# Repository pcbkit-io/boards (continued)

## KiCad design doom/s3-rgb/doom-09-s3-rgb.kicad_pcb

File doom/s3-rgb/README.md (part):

# 09 · s3-rgb — a 4.3" RGB-panel Doom on the ESP32-S3's LCD_CAM

The big-screen variant: the ESP32-S3 scans a **raw RGB TFT** (no controller, no frame memory) out of
a frame buffer in its octal PSRAM with the LCD_CAM peripheral and DMA — the architecture of the
popular ESP32-S3 "4.3-inch" boards. Ten buttons on an I2C expander (the pins all go to the panel),
stereo sound through a DAC and an amplifier, and two 18650 cells it charges from its USB-C port.
JLCPCB assembles everything (matte black mask, ENIG, plated edges); the panel is plugged in and
taped on by hand.

| | |
|---|---|
| Processor | ESP32-S3-WROOM-1-N16R8 (2 × Xtensa LX7 240 MHz, 512 KB SRAM, 16 MB flash, 8 MB octal PSRAM) |
| Display | Newhaven **NHD-4.3-480272EF-ASXP** (IPS; the ASXN it replaces is discontinued): 4.3" 480 × 272, 24-bit RGB parallel, SYNC-DE mode at 8.9 MHz (HSYNC 4 + 39 + 480 + 8, VSYNC 4 + 8 + 272 + 8: 57 Hz, the sheet's typical timing; its line must last 55–65 µs); driven as RGB565 (R3–R7 IO1/2/4/5/6, G2–G7 IO7/15/16/17/18/8, B3–B7 IO9–IO13; PCLK IO42, DE IO40, VSYNC IO41, HSYNC IO39; the low bits grounded) through a 40-pin 0.5 mm FFC connector (Hirose FH34SRJ-40S-0.5SH, top and bottom contacts, 1 mm high) on the front under the panel: the panel's cable folds back under it into the connector, Newhaven's own arrangement |
| Backlight | 12 white LEDs, 25.6 V at 40 mA: **MT3608 boost as a constant-current driver** from SYS (FB regulates 0.6 V over 15 Ω), EN/PWM on IO46 (a strap that must be low at reset: 100 kΩ pull-down); two 2 % zeners in series (18 V + 10 V, 27.3–28.6 V) into FB through 1 kΩ hold the output under the switch's 30 V when no panel is plugged in |
| Input | 10 tact switches on an **MCP23017** (I2C 0x20, IO14 SDA, IO38 SCL), interrupt on change to IO3 |
| Sound | I2S (IO47 BCK, IO48 LRCK, IO21 DIN) → **PCM5102A** DAC → **PAM8403** stereo class-D from SYS (SHDN on 3.3 V: asleep when switched off) (100 kΩ before each input: at most 0.8 W) → two 15 × 15 mm SMD speakers (FS-1540, 8 Ω, C482341) on the back at the two ends, assembled by JLCPCB |
| Power | **2 × 18650 Li-ion in parallel** (1S2P, a 2 A resettable fuse per cell) behind a reverse-cell P-FET (AO3401A) and DW01A + FS8205A protection; USB-C (1 A PTC fuse, TVS, ESD array) → **BQ24075** charger with power path → SYS for the backlight driver and the amplifier → **TLV75733** low-dropout regulator (1 A) for 3.3 V; on/off slide switch on the regulator's EN |
| Programming | USB-C D+/D− to the S3's native USB (IO19/IO20): esptool over USB-Serial/JTAG; RESET (EN) and BOOT (IO0) buttons on the back |
| Board | 182 × 80 mm, **4 layers**, matte black mask, white silkscreen, ENIG, plated edges, four M3 holes; front: the panel on 3 mm foam tape (outline in the silkscreen) over its FFC connector, buttons, the power corner (USB-C at the top edge, charger, CHG/USB LEDs, on/off switch); back: two 18650 holders along the bottom edge, module (antenna past the top edge), protection, regulator, backlight driver, expander, audio, the two speakers, test pads; the PCBKit mark (front, under the D-pad), pcbkit.io (front, between the right-hand buttons); no reference designators on the front |

<!-- STATUS -->
**Board status** (measured on the dev host with PCBKit's CLI): `pcbkit check`: complete — 0 errors, 3 warnings (erc-rail-name), 0 unrouted nets. 106 components, 91 nets, 923 track segments (3760 mm), 135 vias.
`analysis.run { lens: "ready" }`: Typical scenario from the parts' datasheets. Nothing to fix, 4 to consider, 16 ok: weigh the warnings (tell the person about the ones that are their choice), then the board is ready to order.
`pcbkit export --format fab` succeeds without `--force`: every assembled line of the BOM has an LCSC code.
<!-- /STATUS -->

What `check` and the ready lens leave to weigh, and why each is acceptable:

| Warning | Why it is acceptable |
|---|---|
| `diff-pair-uncoupled`, `skew`: DP / DN 18 mm uncoupled (126 mm coupled), 0.7 mm apart in length | USB full speed (12 Mbit/s): the connector is at the top left, the module at the top right; the uncoupled stretch is at the two ends, harmless at 4–20 ns edges |
| BAT's copper heats up by 10 °C (1 A on its thinnest track) | 1 A is the charger's worst case into flat cells; in play the cells give about 0.6 A |
| 6 heat sources need exact thermal parameters | the regulator, charger, boost, amplifier, DAC and module dissipate well under 0.5 W each in this design; the estimate uses generic package limits, as for every board here |

## Run it in the browser

Open https://app.pcbkit.io/github/pcbkit-io/boards/tree/main/doom/s3-rgb, open the
Laboratory and press **Build & run**: the page builds `doom/` for the ESP32-S3's Xtensa LX7 with
Espressif's LLVM (with `DOOM1.WAD` linked into its flash), boots it the way the chip's boot ROM
boots an image from flash, and shows on the panel the frames LCD_CAM scans out of the PSRAM. The
buttons reach the program through the MCP23017, as on the board. Play with the keyboard (arrows,
F fire, Space use, comma/period strafe, M menu, Enter) or a gamepad (`input.js`).

## Why it runs Doom (and what the screen costs)

Doom is the same port as variant 08 (the program and the WAD in place in flash, the zone heap,
screens and visplanes in the octal PSRAM, here at 40 MHz). The difference is the display: the
LCD_CAM peripheral in RGB mode streams a 480 × 272 RGB565 frame buffer from the PSRAM by GDMA
without end, at an 8.9 MHz pixel clock with the Newhaven sheet's typical timing (HSYNC 4 + 39 + 480 + 8,
VSYNC 4 + 8 + 272 + 8): 57 Hz, 261 KB a frame, about 15 MB/s of the PSRAM's ~40 MB/s at 40 MHz
octal DDR (estimate). Each Doom frame is scaled 1.36 times through the palette into the middle
435 × 272 of that buffer and written back from the data cache (the DMA reads the PSRAM, not the
cache). The panel never stops refreshing, which is why this design matters to the simulator: the
display is a **timed bus master**, not a sequence of SPI commands. The ten buttons are read from
the MCP23017 over I2C0 (400 kHz) once a tic. Measured in PCBKit's simulator: the title by 4 s of
device time, the demo by 9 s; 16 s simulated in 12 s.

## Power

Two 18650 Li-ion cells in Keystone 1042 holders on the back, end to end along the bottom edge, in
parallel (1S2P, 3.0–4.2 V, about 5–7 Ah together). From the cells to the loads:

- **Boards ordered before 2026-10-30** (the five of JLCPCB order W2026102705013253) have no per-cell
  fuses and a 28 V 5 % zener on the backlight: put the cells in one at a time and check each against
  the silkscreen's + before inserting the other.
- **Reverse cells:** an AO3401A P-MOSFET in the plus line, its gate at the cells' minus: cells put
  in backwards leave it off and the board unpowered (it conducts both ways when they are right, so
  charging goes through it too). One cell reversed against the other is what the **per-cell fuses**
  are for: each holder's + reaches the pack through its own 2 A resettable fuse (Littelfuse
  1812L200/16GR: 16 V, 100 A interrupting), so a cell put in backwards, or one much fuller than
  the other, trips both in milliseconds instead of shorting the two cells together (tens of
  amperes); take the cell out and they reset. Still put each cell's + at the end the silkscreen
  marks.
- **Protection:** DW01A + FS8205A in the pack's minus: over-charge 4.3 V, over-discharge 2.4 V,
  over-current about 3 A and short circuit, for the pack. Flat-top unprotected 18650 cells fit
  the holders.
- **USB-C input:** 5.1 kΩ on CC1 and CC2 (a sink: 5 V from any charger or computer), a 1 A
  resettable fuse, a 5 V TVS on VBUS and a USBLC6 on D+/D−.
- **Charger with power path:** a TI BQ24075 in USB500 mode (at most 500 mA from the port), 800 mA
  fast charge (RISET 1.13 kΩ), input limit by RILIM 1.18 kΩ, safety timers off (two cells in
  parallel charge longer than its longest timer; termination is by current), TS tied to 10 kΩ (no
  thermistor). Its output SYS runs the board from USB when one is plugged in and from the cells
  through its battery FET otherwise; with more load than USB gives, the cells make up the rest.
- **SYS** feeds the MT3608 backlight driver and the PAM8403 directly (no 5 V rail: both run from
  2.8–5.5 V), and a **TLV75733** (1 A, so the module's 500 mA radio peaks have room; 425 mV
  dropout at 1 A, under 100 mV at this board's ~200 mA) for 3.3 V. It holds 3.3 V down to about 3.4 V of cell; below that the rail follows the
  cells down to 3.0 V, where the ESP32-S3 (3.0–3.6 V) still runs and the cells have under 5 % left.
  The AMS1117 it replaces needs 1.1 V of headroom: straight from the cells it would never make 3.3 V.
- **On/off:** the slide switch on the left edge drives the regulator's EN (100 kΩ holds it low
  between positions). Off, 3.3 V is gone: the module, panel logic, expander and DAC are unpowered,
  the backlight driver's EN is pulled low and the amplifier's SHDN (on 3.3 V) puts it to sleep; the
  cells still charge.

| State | Current (estimate) |
|---|---|
| ESP32-S3 + PSRAM streaming the panel | ~120 mA at 3.3 V |
| Panel logic | 25 mA at 3.3 V |
| Backlight 25.6 V × 40 mA ≈ 1.0 W | ~320 mA from 3.7 V at 85 % |
| PAM8403, moderate volume | ~100 mA |
| **Typical** | **≈ 2.3 W → ~620 mA at 3.7 V** |

Two 3000 mAh cells → **about 9 h** of play (estimate). The TLV75733 burns (3.7 − 3.3) × 0.15 A ≈
0.06 W from the cells (0.3 W from USB).

## Charging

Plug a USB-C charger or computer into the port at the top left. The red LED (CHG) is on while the
cells charge and goes out when they are full; the green LED (USB) is on while USB power is
present. Switched off, the cells take what the port allows in USB500 mode, just under 500 mA: two empty
3000 mAh cells take about 13 h (overnight). Playing
while plugged in, the board takes about 600 mA, more than USB500 mode draws, so the cells hold or
slowly discharge instead of charging. Insert the cells with + at the end the back's silkscreen marks.

## Modules plugged in by hand

- **DS1: the panel**, Newhaven NHD-4.3-480272EF-ASXP (DigiKey, Mouser; its cable and pinout are the
  discontinued ASXN's), bought separately. Lay it face down above the board's top
  edge, its cable toward the board, and push the cable's end straight into J1 (J1 has contacts on
  both sides: either face of the cable works), then close J1's lever. Turn the panel over onto
  the board along the cable's fold and tape it inside its silkscreen outline with 3 mm double-sided
  foam tape on its frame (keep the tape off the cable): the cable then lies folded under the panel,
  as Newhaven's drawing has it. J1 (1 mm high) sits under the panel, and so does one of BT2's
  locating holes (keep the tape clear of it). The panel lies turned half a turn (its cable side,
  the bottom of its scan, at the board's top edge), so the firmware sends the frame out from its
  last pixel to its first.
- **Two 18650 cells.**

## Firmware: build and flash

- **Build:** in PCBKit, the Laboratory's **Build & run** builds `doom/` (Xtensa LX7, Espressif's
  LLVM, the kit's start-up, LCD_CAM/GDMA and I2C drivers); then export the firmware
  (`export.run { format: "firmware" }`): `U1.bin`, the whole flash from offset 0. No 2nd-stage
  bootloader or partition table: the ROM boots the image directly.
- **Flashing on arrival:** switch the board on and plug the USB-C port into a computer: the
  ESP32-S3's built-in USB-Serial/JTAG appears as a serial port (no driver on Linux and macOS; on
  Windows 10+ the class driver); `esptool.py --chip esp32s3 write_flash 0x0 U1.bin` resets it into
  the ROM loader by itself. A fresh module's flash is empty and its ROM loader answers at once. If
  firmware ever takes the USB pins over, hold BOOT (IO0) on the back, press RESET (EN), release
  BOOT: the ROM loader is back. Press RESET: Doom starts.

## Bill of materials

Rough cost at 10 pieces (estimates): ESP32-S3-WROOM-1-N16R8 $4.50 · NHD-4.3-480272EF-ASXP $29 · Hirose
FH34SRJ-40S-0.5SH $0.40 · MT3608 $0.15 · MCP23017 $1.20 ·
PCM5102A $2.00 · PAM8403 $0.15 · BQ24075, protection and TLV75733 $1.60 · USB-C $0.40 · buttons
$3.40 · passives $1.80 · two 18650 holders $9.80 · 4-layer PCB $6.00 · 2 SMD speakers $1.60 → **about
$71** with the Newhaven panel, ~$44 with a generic one, without the cells.

<!-- BOM -->
The assembly BOM as `pcbkit export --format fab` writes it (JLCPCB assembly: LCSC codes; the modules' lines are their sockets):

| Qty | Refs | Part | LCSC | Footprint |
|---|---|---|---|---|
| 2 | BT1, BT2 | 1042 | C5249310 | BatteryHolder_Keystone_1042_1x18650 |
| 1 | C1 | 10uF | C19702 | C_0603_1608Metric |
| 1 | C2 | 22uF | C45783 | C_0805_2012Metric |
| 1 | C3 | 4.7uF | C29823 | C_1206_3216Metric |
| 2 | C4, C22 | 22uF | C12891 | C_1206_3216Metric |
| 7 | C5, C7, C8, C10, C12, C16, C26 | 100nF | C1525 | C_0402_1005Metric |
| 5 | C6, C19, C20, C21, C23 | 1uF | C52923 | C_0402_1005Metric |
| 3 | C9, C11, C13 | 10uF | C15850 | C_0805_2012Metric |
| 2 | C14, C15 | 2.2uF | C87994 | C_0805_2012Metric |
| 2 | C17, C18 | 2.2nF | C1531 | C_0402_1005Metric |
| 2 | C24, C25 | 470nF | C47339 | C_0402_1005Metric |
| 3 | C33, C34, cIn | 1uF | C15849 | C_0603_1608Metric |
| 1 | D1 | 1N5819HW-7-F | C82544 | D_SOD-123 |
| 1 | D2 | zener 18V | C150102 | D_SOD-323 |
| 1 | D3 | zener 10V | C209565 | D_SOD-323 |
| 1 | D6 | tvs 5V | C918844 | D_SOD-323 |
| 1 | F1 | PTC 750mA | C20800 | Fuse_1206_3216Metric |
| 2 | F2, F3 | PTC 2000mA | C18198340 | Fuse_1812_4532Metric |
| 1 | J1 | FH34SRJ-40S-0.5SH(50) | C506798 | Hirose_FH34SRJ-40S-0.5SH_1x40-1MP_P0.50mm_Horizontal |
| 1 | J3 | USB4105-GF-A | C165948 | USB_C_Receptacle_USB2.0_16P |
| 1 | L1 | 22uH | C83472 | L_Power_4x4mm |
| 2 | LS1, LS2 | FS-1540 | C482341 | Speaker_FUET_FS-1540_15x15mm |
| 1 | Q1 | AO3401A | C15127 | SOT-23 |
| 1 | Q2 | FS8205A | C5148694 | TSSOP-8_4.4x2.93mm_P0.65mm |
| 4 | R1, R3, R4, rTs | 10kohm | C25744 | R_0402_1005Metric |
| 5 | R2, R11, R14, R16, R17 | 100kohm | C25741 | R_0402_1005Metric |
| 2 | R5, R6 | 4.7kohm | C25900 | R_0402_1005Metric |
| 2 | R7, R8 | 470ohm | C25117 | R_0402_1005Metric |
| 2 | R9, R10 | 5.1kohm | C25905 | R_0402_1005Metric |
| 1 | R12 | 100ohm | C25076 | R_0402_1005Metric |
| 2 | R13, R15 | 1kohm | C11702 | R_0402_1005Metric |
| 1 | RS1 | 15ohm | C22810 | R_0603_1608Metric |
| 12 | SW1, SW2, SW3, SW4, SW5, SW6, SW7, SW8, SW9, SW10, SW12, SW13 | PTS645SM43SMTR92 LFS | C221880 | SW_Tactile_SPST_6x6mm_SMD |
| 1 | SW11 | MSK12C02 | C431540 | SW_Slide_SPDT_Shouhan_MSK12C02 |
| 1 | U1 | ESP32-S3-WROOM-1-N16R8 | C2913202 | ESP32-S3-WROOM-1_module_18x25.5mm_40_edge_pads_EPAD |
| 1 | U2 | DW01A | C351410 | SOT-6_1.6x2.9mm_P0.95mm |
| 1 | U3 | MCP23017-E/SO | C47023 | SOIC-28W_7.5x17.9mm_P1.27mm |
| 1 | U4 | PCM5102APWR | C107671 | TSSOP-20_4.4x6.5mm_P0.65mm |
| 1 | U5 | PAM8403DR | C17337 | SOIC-16_3.9x9.9mm_P1.27mm |
| 1 | U6 | TLV75733PDBVR | C485517 | SOT-23-5 |
| 1 | U7 | BQ24075RGTR | C15464 | QFN-16-1EP_3x3mm_P0.5mm_EP1.68x1.68mm |
| 1 | U8 | MT3608 | C84817 | SOT-23-6 |
| 1 | U9 | USBLC6-2SC6 | C7519 | SOT-23-6 |
| 2 | cBat, cSys | 4.7uF | C1779 | C_0805_2012Metric |
| 1 | ledChg | red | C2286 | LED_0603_1608Metric |
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
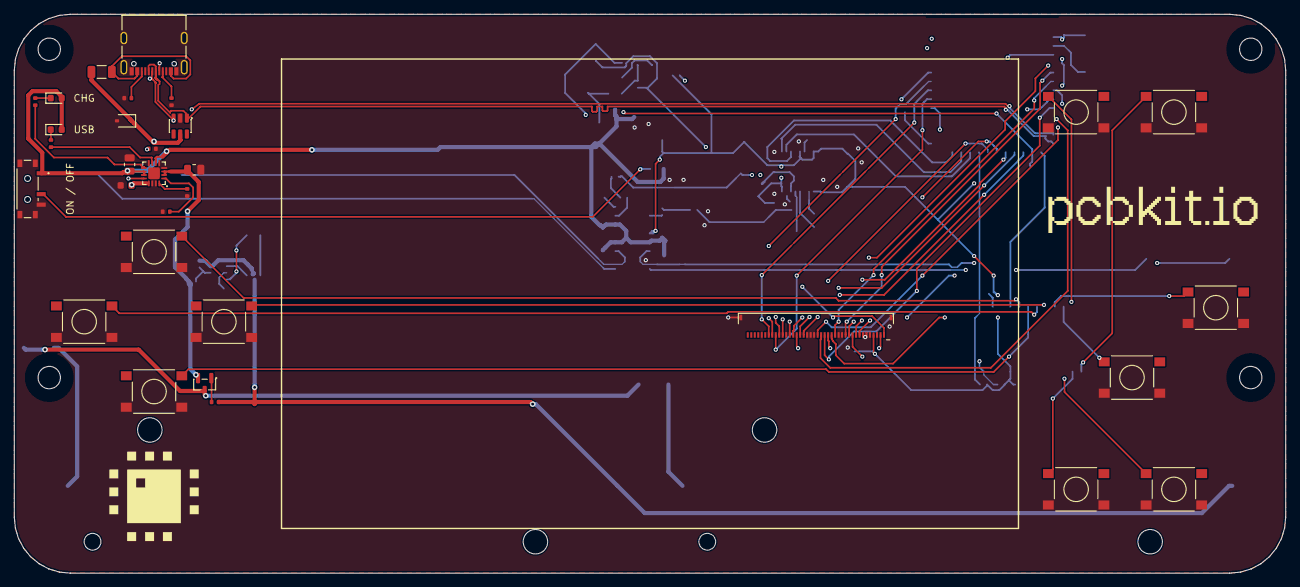
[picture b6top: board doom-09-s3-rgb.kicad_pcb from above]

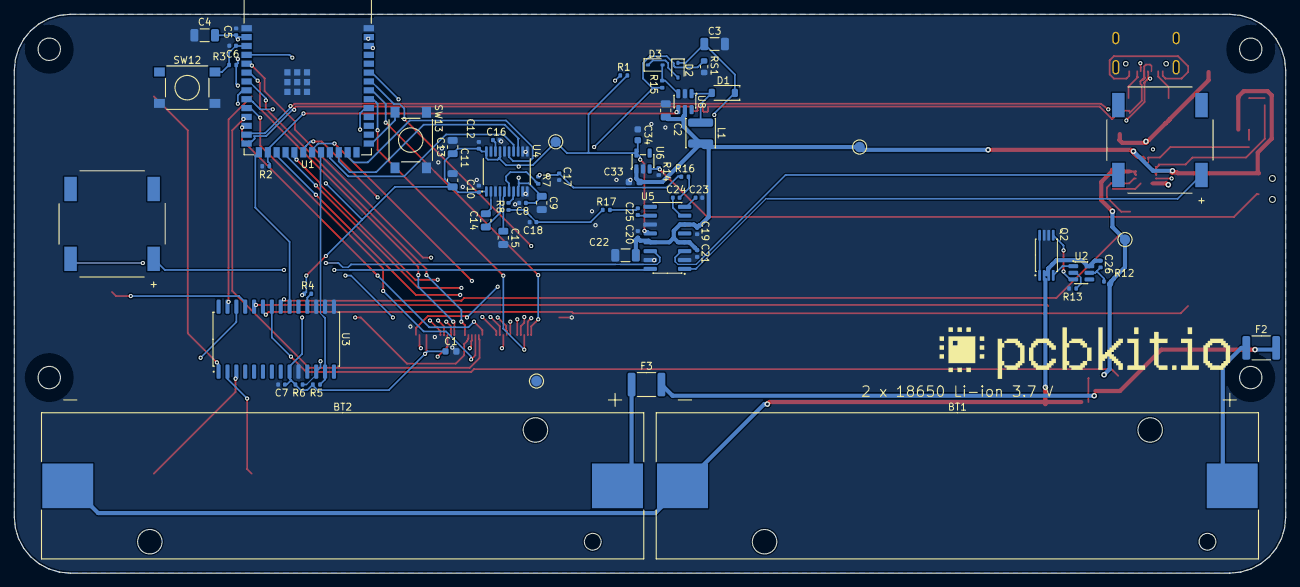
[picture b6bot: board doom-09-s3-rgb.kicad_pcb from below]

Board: 4 copper layers, 182.0 x 80.0 mm, 106 parts (68 on the bottom side), 91 nets.

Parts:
BT1, BT2: 1042; BatteryHolder_Keystone_1042_1x18650
C1: 10uF; C_0603_1608Metric
C2: 22uF; C_0805_2012Metric
C3: 4.7uF; C_1206_3216Metric
C4, C22: 22uF; C_1206_3216Metric
C5, C7, C8, C10, C12, C16, C26: 100nF; C_0402_1005Metric
C6, C19, C20, C21, C23: 1uF; C_0402_1005Metric
C9, C11, C13: 10uF; C_0805_2012Metric
C14, C15: 2.2uF; C_0805_2012Metric
C17, C18: 2.2nF; C_0402_1005Metric
C24, C25: 470nF; C_0402_1005Metric
C33, C34: 1uF; C_0603_1608Metric
D1: 1N5819HW-7-F; D_SOD-123
D2: zener 18V; D_SOD-323
D3: zener 10V; D_SOD-323
D6: tvs 5V; D_SOD-323
DS1: NHD-4.3-480272EF-ASXP; Newhaven_NHD-4.3-480272EF_Panel
F1: PTC 750mA; Fuse_1206_3216Metric
F2, F3: PTC 2000mA; Fuse_1812_4532Metric
H1, H2, H3, H4: MountingHole_3.2mm_M3
J1: FH34SRJ-40S-0.5SH(50); Hirose_FH34SRJ-40S-0.5SH_1x40-1MP_P0.50mm_Horizontal
J3: USB4105-GF-A; USB_C_Receptacle_USB2.0_16P
L1: 22uH; L_Power_4x4mm
LS1, LS2: FS-1540; Speaker_FUET_FS-1540_15x15mm
Q1: AO3401A; SOT-23
Q2: FS8205A; TSSOP-8_4.4x2.93mm_P0.65mm
R1, R3, R4: 10kohm; R_0402_1005Metric
R2, R11, R14, R16, R17: 100kohm; R_0402_1005Metric
R5, R6: 4.7kohm; R_0402_1005Metric
R7, R8: 470ohm; R_0402_1005Metric
R9, R10: 5.1kohm; R_0402_1005Metric
R12: 100ohm; R_0402_1005Metric
R13, R15: 1kohm; R_0402_1005Metric
RS1: 15ohm; R_0603_1608Metric
SW1, SW2, SW3, SW4, SW5, SW6, SW7, SW8, SW9, SW10, SW12, SW13: PTS645SM43SMTR92 LFS; SW_Tactile_SPST_6x6mm_SMD
SW11: MSK12C02; SW_Slide_SPDT_Shouhan_MSK12C02
U1: ESP32-S3-WROOM-1-N16R8; ESP32-S3-WROOM-1_module_18x25.5mm_40_edge_pads_EPAD
U2: DW01A; SOT-6_1.6x2.9mm_P0.95mm
U3: MCP23017-E/SO; SOIC-28W_7.5x17.9mm_P1.27mm
U4: PCM5102APWR; TSSOP-20_4.4x6.5mm_P0.65mm
U5: PAM8403DR; SOIC-16_3.9x9.9mm_P1.27mm
U6: TLV75733PDBVR; SOT-23-5
U7: BQ24075RGTR; QFN-16-1EP_3x3mm_P0.5mm_EP1.68x1.68mm
U8: MT3608; SOT-23-6
U9: USBLC6-2SC6; SOT-23-6
cBat: 4.7uF; C_0805_2012Metric
cIn: 1uF; C_0603_1608Metric
cSys: 4.7uF; C_0805_2012Metric
ledChg: red; LED_0603_1608Metric
ledPg: green; LED_0603_1608Metric
logo: Logo_PCBKit_pcbkit.io
mark: Logo_PCBKit_mark
rChg: 1.5kohm; R_0402_1005Metric
rIlim: 1.18kohm; R_0402_1005Metric
rIset: 1.13kohm; R_0402_1005Metric
rPg: 1.5kohm; R_0402_1005Metric
rTs: 10kohm; R_0402_1005Metric
tpBat: TestPoint_Round_D1.5mm
tpGnd: TestPoint_Round_D1.5mm
tpSys: TestPoint_Round_D1.5mm
tpV3: TestPoint_Round_D1.5mm
wordmark: Logo_PCBKit_wordmark

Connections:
AMP_L: C24.2 (b), R16.2 (b)
AMP_R: C25.2 (b), R17.2 (b)
BAT: Q1.2 (S), R12.1 (a), U7.2 (BAT), U7.3 (BAT), cBat.1 (a), tpBat.1
BAT_IN: F2.2 (b), F3.2 (b), Q1.3 (D)
BLU3: J1.24 (B3), U1.17 (IO9)
BLU4: J1.25 (B4), U1.18 (IO10)
BLU5: J1.26 (B5), U1.19 (IO11)
BLU6: J1.27 (B6), U1.20 (IO12)
BLU7: J1.28 (B7), U1.21 (IO13)
BL_EN: R2.1 (a), U1.16 (IO46), U8.4 (EN)
BL_FB: D3.2 (A), R15.2 (b), U8.3 (FB)
BL_OVP: D2.2 (A), D3.1 (K)
BL_SW: D1.2 (A), L1.2 (b), U8.1 (SW)
CELL1_P: BT1.2 (C2), F2.1 (a)
CELL2_P: BT2.2 (C2), F3.1 (a)
CELL_N: BT1.1 (C1), BT2.1 (C1), C26.1 (a), Q2.2 (S1), Q2.3 (S1), R11.1 (a), U2.6 (GND)
CHG_LED: ledChg.1 (K), rChg.2 (b)
CHG_N: U7.9 (nCHG), rChg.1 (a)
DAC_1V8: C16.1 (a), U4.18 (LDOO)
DAC_VNEG: C15.1 (a), U4.5 (VNEG)
DE: J1.34 (DEN), U1.33 (IO40)
DISP: J1.31 (DISP), R1.2 (b)
DN: J3.A7 (DN), J3.B7 (DN), U1.13 (IO19), U9.3 (IO2)
DOWN: SW2.1 (a), U3.22 (GPA1)
DP: J3.A6 (DP), J3.B6 (DP), U1.14 (IO20), U9.1 (IO1)
EN: C6.1 (a), R3.2 (b), SW12.1 (a), U1.3 (EN)
ENTER: SW10.1 (a), U3.3 (GPB2)
FIRE: SW7.1 (a), U3.25 (GPA4)
GND: C1.2 (b), C2.2 (b), C3.2 (b), C4.2 (b), C5.2 (b), C6.2 (b), C7.2 (b), C8.2 (b), C9.2 (b), C10.2 (b), C11.2 (b), C12.2 (b), C13.2 (b), C15.2 (b), C16.2 (b), C17.2 (b), C18.2 (b), C19.2 (b), C20.2 (b), C21.2 (b), C22.2 (b), C23.2 (b), C33.2 (b), C34.2 (b), D6.2 (A), J1.3 (GND), J1.5 (R0), J1.6 (R1), J1.7 (R2), J1.13 (G0), J1.14 (G1), J1.21 (B0), J1.22 (B1), J1.23 (B2), J1.29 (GND), J1.36 (GND), J1.MP, J3.A1 (GND), J3.A12, J3.B1 (GND), J3.B12, J3.S1 (SHIELD), Q2.6 (S2), Q2.7 (S2), R2.2 (b), R9.2 (b), R10.2 (b), R13.2 (b), R14.2 (b), RS1.2 (b), SW1.2 (b), SW2.2 (b), SW3.2 (b), SW4.2 (b), SW5.2 (b), SW6.2 (b), SW7.2 (b), SW8.2 (b), SW9.2 (b), SW10.2 (b), SW11.3 (B), SW11.4 (SHELL), SW12.2 (b), SW13.2 (b), U1.1 (GND), U1.40 (GND), U1.41 (GND), U3.10 (VSS), U3.15 (A0), U3.16 (A1), U3.17 (A2), U4.3 (CPGND), U4.9 (AGND), U4.10 (DEMP), U4.11 (FLT), U4.12 (SCK), U4.16 (FMT), U4.19 (DGND), U5.2 (PGND), U5.11 (GND), U5.15 (PGND), U6.2 (GND), U7.4 (nCE), U7.5 (EN2), U7.8 (VSS), U7.14 (TMR), U7.15 (SYSOFF), U7.17 (VSS), U8.2 (GND), U9.2 (GND), cBat.2 (b), cIn.2 (b), cSys.2 (b), rIlim.2 (b), rIset.2 (b), rTs.2 (b), tpGnd.1
GRN2: J1.15 (G2), U1.7 (IO7)
GRN3: J1.16 (G3), U1.8 (IO15)
GRN4: J1.17 (G4), U1.9 (IO16)
GRN5: J1.18 (G5), U1.10 (IO17)
GRN6: J1.19 (G6), U1.11 (IO18)
GRN7: J1.20 (G7), U1.12 (IO8)
HSYNC: J1.32 (HSYNC), U1.32 (IO39)
I2S_BCK: U1.24 (IO47), U4.13 (BCK)
I2S_DIN: U1.23 (IO21), U4.14 (DIN)
I2S_LRCK: U1.25 (IO48), U4.15 (LRCK)
ILIM: U7.12 (ILIM), rIlim.1 (a)
ISET: U7.16 (ISET), rIset.1 (a)
KEYS_INT: U1.15 (IO3), U3.20 (INTA)
LDO_EN: R14.1 (a), SW11.2 (COM), U6.3 (EN)
LED_A: C3.1 (a), D1.1 (K), D2.1 (K), J1.2 (LED_A)
LED_K: J1.1 (LED_K), R15.1 (a), RS1.1 (a)
LEFT: SW3.1 (a), U3.23 (GPA2)
LINE_L: C17.1 (a), R7.1 (a), R16.1 (a)
LINE_R: C18.1 (a), R8.1 (a), R17.1 (a)
MENU: SW9.1 (a), U3.2 (GPB1)
unnamed: C14.2 (b), U4.2 (CAPP)
unnamed: C14.1 (a), U4.4 (CAPM)
unnamed: C23.1 (a), U5.8 (VREF)
unnamed: C24.1 (a), U5.7 (INL)
unnamed: C25.1 (a), U5.10 (INR)
unnamed: C26.2 (b), R12.2 (b), U2.5 (VCC)
unnamed: Q2.4 (G1), U2.1 (OD)
unnamed: Q2.5 (G2), U2.3 (OC)
unnamed: R4.2 (b), U3.18 (RESET)
unnamed: R7.2 (b), U4.6 (OUTL)
unnamed: R8.2 (b), U4.7 (OUTR)
unnamed: R13.1 (a), U2.2 (CS)
unnamed: SW13.1 (a), U1.27 (IO0)
PCLK: J1.30 (CLK), U1.35 (IO42)
PG_LED: ledPg.1 (K), rPg.1 (a)
PG_N: U7.7 (nPGOOD), rPg.2 (b)
RED3: J1.8 (R3), U1.39 (IO1)
RED4: J1.9 (R4), U1.38 (IO2)
RED5: J1.10 (R5), U1.4 (IO4)
RED6: J1.11 (R6), U1.5 (IO5)
RED7: J1.12 (R7), U1.6 (IO6)
RIGHT: SW4.1 (a), U3.24 (GPA3)
SCL: R6.1 (a), U1.31 (IO38), U3.12 (SCL)
SDA: R5.1 (a), U1.22 (IO14), U3.13 (SDA)
SPK_LN: LS1.1 (N), U5.3 (OUTLN)
SPK_LP: LS1.2, U5.1 (OUTLP)
SPK_RN: LS2.1 (N), U5.14 (OUTRN)
SPK_RP: LS2.2, U5.16 (OUTRP)
STRAFE_L: SW5.1 (a), U3.27 (GPA6)
STRAFE_R: SW6.1 (a), U3.1 (GPB0)
SYS: C2.1 (a), C19.1 (a), C20.1 (a), C21.1 (a), C22.1 (a), C33.1 (a), L1.1 (a), SW11.1 (A), U5.4 (PVDD), U5.6 (VDD), U5.13 (PVDD), U6.1 (IN), U7.6 (EN1), U7.10 (OUT), U7.11 (OUT), U8.5 (VIN), cSys.1 (a), ledChg.2 (A), ledPg.2 (A), tpSys.1
TS: U7.1 (TS), rTs.1 (a)
U2Support/DRAIN: Q2.1 (D12), Q2.8 (D12)
UP: SW1.1 (a), U3.21 (GPA0)
USE: SW8.1 (a), U3.26 (GPA5)
V3: C1.1 (a), C4.1 (a), C5.1 (a), C7.1 (a), C8.1 (a), C9.1 (a), C10.1 (a), C11.1 (a), C12.1 (a), C13.1 (a), C34.1 (a), J1.4 (VDD), R1.1 (a), R3.1 (a), R4.1 (a), R5.2 (b), R6.2 (b), U1.2 (P3V3), U3.9 (VDD), U4.1 (CPVDD), U4.8 (AVDD), U4.17 (XSMT), U4.20 (DVDD), U5.12 (SHDN), U6.5 (OUT), tpV3.1
VBUS: D6.1 (K), F1.2 (b), U7.13 (IN), U9.5 (VBUS), cIn.1 (a)
VSYNC: J1.33 (VSYNC), U1.34 (IO41)
reversed/gate: Q1.1 (G), R11.2 (b)
usb/power/cc1: J3.A5 (CC1), R9.1 (a)
usb/power/cc2: J3.B5 (CC2), R10.1 (a)
usb/power/vbusIn: F1.1 (a), J3.A4 (VBUS), J3.A9, J3.B4 (VBUS), J3.B9

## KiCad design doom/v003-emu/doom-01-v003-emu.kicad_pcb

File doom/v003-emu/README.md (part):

# 01 · v003-emu — Doom on a 10-cent RISC-V, by emulation

The most primitive variant: a WCH CH32V003 cannot hold Doom (2 KB of RAM), so it does not try.
Its firmware is a small RV32IMA interpreter; the real program — Doom built for a plain RV32 machine
— lives in an 8 MB SPI PSRAM and boots from a 16 MB SPI flash. It is the "Linux on an 8-bit AVR"
trick applied to Doom: slow (well under one frame per second, estimate below), but every part is a
real, orderable chip, and it is the clearest test of whether PCBKit's engine models *buses* rather
than *programs*.

| | |
|---|---|
| Processor | WCH CH32V003F4P6, QingKe V2A core: RISC-V **RV32EC** (16 registers, compressed) + WCH's XW byte/halfword extension, 48 MHz (24 MHz HSI × 2 PLL), 2 KB SRAM, 16 KB flash, TSSOP-20 |
| Memory | APS6404L-3SQR 8 MB PSRAM (guest RAM) and W25Q128JV 16 MB NOR flash (guest kernel + WAD), both on SPI1 (PC5/PC6/PC7) with their own chip selects (PC0, PC4) |
| Display | Nokia 5110 module, PCD8544, 84 × 48 monochrome, SPI shared with the memories (CS PC3, D/C PC2), reset by RC at power-up |
| Input | 8 tact switches (5.1 mm) to GND, internal pull-ups: PD0, PD2–PD6, PA1, PA2 (the crystal pins are free: the HSI runs the chip) |
| Sound | passive piezo on PC1 (TIM2 CH4 remap) |
| Power | 2 × 18650 Li-ion in parallel (1S2P, a 2 A resettable fuse per cell) behind reverse-cell (AO3401A) and DW01A + FS8205A protection; BQ24075 charger with power path from a USB-C port (fuse, TVS); SYS → AP2112K-3.3 LDO, its enable on the slide switch |
| Programming | WCH single-wire debug (SDI) on PD1: J2, a 3-pin header (3V3, SWIO, GND) at the right edge of the back for a WCH-LinkE |
| Board | 96 × 92 mm, 2 layers, four M3 holes; front: LCD, buttons, USB-C, charger, switch, test pads; back: two 18650 holders, the processor and its memories, piezo, J2 |

<!-- STATUS -->
**Board status** (measured on the dev host with PCBKit's CLI): `pcbkit check`: complete — 0 errors, 2 warnings (erc-rail-name), 0 unrouted nets. 69 components, 48 nets, 440 track segments (1361 mm), 40 vias.
`analysis.run { lens: "ready" }`: Typical scenario, partial. Nothing to fix, 2 to consider, 17 ok: weigh the warnings (tell the person about the ones that are their choice), then the board is ready to order.
`pcbkit export --format fab` succeeds without `--force`: every assembled line of the BOM has an LCSC code.
<!-- /STATUS -->

## Run it in the browser

Open https://app.pcbkit.io/github/pcbkit-io/boards/tree/main/doom/v003-emu, open the
Laboratory and press **Build & run**: the page builds both programs — `emu/` for the CH32V003
(RV32EC) and `doom/` for the computer it emulates (pcbkit-virt, with `DOOM1.WAD` linked in) — puts
the second in the W25Q128 and runs the board. Until the first frame the LCD shows Doom's start-up
messages; the title screen comes after about three minutes of device time, then the demo.

## Why it can (barely) run Doom

The CH32V003's job is only to be a CPU for an emulated one (`emu/`):

1. Its firmware (15.6 KB of its 16 KB flash) is an RV32IMAC interpreter (`emu/rvemu.c`) with a
   direct-mapped write-back cache of 32 lines × 16 bytes in its 2 KB of SRAM.
2. The guest (`doom/`: Doom for pcbkit-virt, an ELF file) is in the W25Q128: its code and
   constants, the WAD linked into them, are read where they lie; its writable segment is copied
   into the PSRAM at boot.
3. Guest loads and stores go through the cache; a miss is one SPI transaction (command, 24-bit
   address and 16 bytes at 24 MHz, 6.7 µs with the chip selected: inside the PSRAM's 8 µs limit).
4. Each guest frame (320 × 200, 8-bit) is scaled to 84 × 48 with ordered dithering and sent to
   the PCD8544; its start-up messages are shown on the glass until then, and a stop says why.

**Speed, measured in PCBKit's simulator** (instruction-accurate CH32V003 at 48 MHz, the memories'
SPI timing): Doom's start-up messages from the first second, its title screen at about 200 s of
device time, the demo at 300 s, then a frame every several seconds. It is a demonstration
board, not a game console — and the reason it is variant 01.

## Power

| State | Current at 3.3 V (estimate) |
|---|---|
| CH32V003 at 48 MHz | ~5 mA |
| PSRAM active (SPI, low clock) | ~3–5 mA (datasheet: 5.5 mA typ at 133 MHz) |
| W25Q128 (only while booting) | ~10 mA |
| PCD8544 + backlight through 330 Ω | ~0.3 mA + ~4 mA |
| **Total** | **~15–20 mA ≈ 60 mW** |

Two 18650 Li-ion cells in Keystone 1042 holders on the back, in parallel (1S2P, 3.0–4.2 V). From
the cells to the chips:

- **Reverse cells:** an AO3401A P-MOSFET in the plus line, its gate at the cells' minus: cells put
  in backwards leave it off and the board unpowered (it conducts both ways when they are right, so
  charging goes through it too). One cell reversed against the other is what the **per-cell fuses**
  are for: each holder's + reaches the pack through its own 2 A resettable fuse (Littelfuse
  1812L200/16GR: 16 V, 100 A interrupting), so a cell put in backwards, or one much fuller than
  the other, trips both in milliseconds instead of shorting the two cells together (tens of
  amperes); take the cell out and they reset. Still put each cell's + at the end the silkscreen
  marks.
- **Protection:** DW01A + FS8205A in the pack's minus: over-charge 4.3 V, over-discharge 2.4 V,
  over-current about 3 A and short circuit, for the pack. Flat-top unprotected 18650 cells fit
  the holders.
- **USB-C input:** a power-only receptacle (5.1 kΩ on CC1 and CC2: any USB-C charger or computer
  gives 5 V), a 750 mA resettable fuse (nSMD075) and a 5 V TVS diode (SMF5.0A) before the charger.
- **Charger with power path:** a TI BQ24075 in USB500 mode (at most 500 mA from the port), ISET
  for 800 mA (RISET 1.13 kΩ), RILIM 1.18 kΩ, safety timers off (two cells in parallel charge longer
  than its longest timer; termination is by current), TS tied to 10 kΩ (no thermistor). A linear
  charger passes on at most what it takes in, so from USB the cells charge at up to about 500 mA.
  Its output SYS runs the board from USB when one is plugged in and from the cells otherwise.
- **3.3 V:** an AP2112K-3.3 LDO from SYS (the old TPS61023 boost cannot make 3.3 V from a Li-ion
  cell above it). At this board's 20 mA its dropout is a few mV, so 3.3 V holds down to about
  3.3 V on the cells and then follows them; every chip here runs from 2.7 V.
- **On/off:** the slide switch at the top edge drives the LDO's enable (1 MΩ pulls it off); the
  charger charges with the switch off. Off, the board draws only the charger's and the protection's
  few µA.

Two 3000 mAh cells (about 22 Wh) at 60 mW: **about 300 h** of (very slow) play (estimate). A
full charge of two empty cells from USB at about 500 mA takes about 12 h.

## Charging

Plug any USB-C charger or computer into J1 at the left edge. The red LED (CHG) is on while the
cells charge and goes out when they are full; the green LED (USB) is on while USB power is
present. The board runs from USB while it charges, switched on or off. Insert the cells with +
at the end the back's silkscreen marks.

## Modules plugged in by hand

The assembly solders a 1x8 female socket for the display; the module is bought separately:

- **DS1: Nokia 5110 LCD module** (PCD8544, 84 × 48, the common red board with an 8-pin header:
  RST, CE, DC, DIN, CLK, VCC, BL, GND in that order), its pins soldered on as it comes, plugged in
  on the front. Boards with another pin order exist: check the order on its silkscreen against
  the board's before plugging it in.

## Firmware: build and flash

- **Build:** in PCBKit, the Laboratory's **Build & run** builds both programs (the CH32V003's with
  RV32EC, ilp32e, -Os; the guest for RV32IMAC with the WAD); then export the firmware
  (`export.run { format: "firmware" }`): `U1.bin` for the CH32V003 and `U3.bin` for the W25Q128.
- **The CH32V003, on arrival:** a WCH-LinkE (about $5, USB) on J2: its 3V3, SWIO and GND to J2's
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
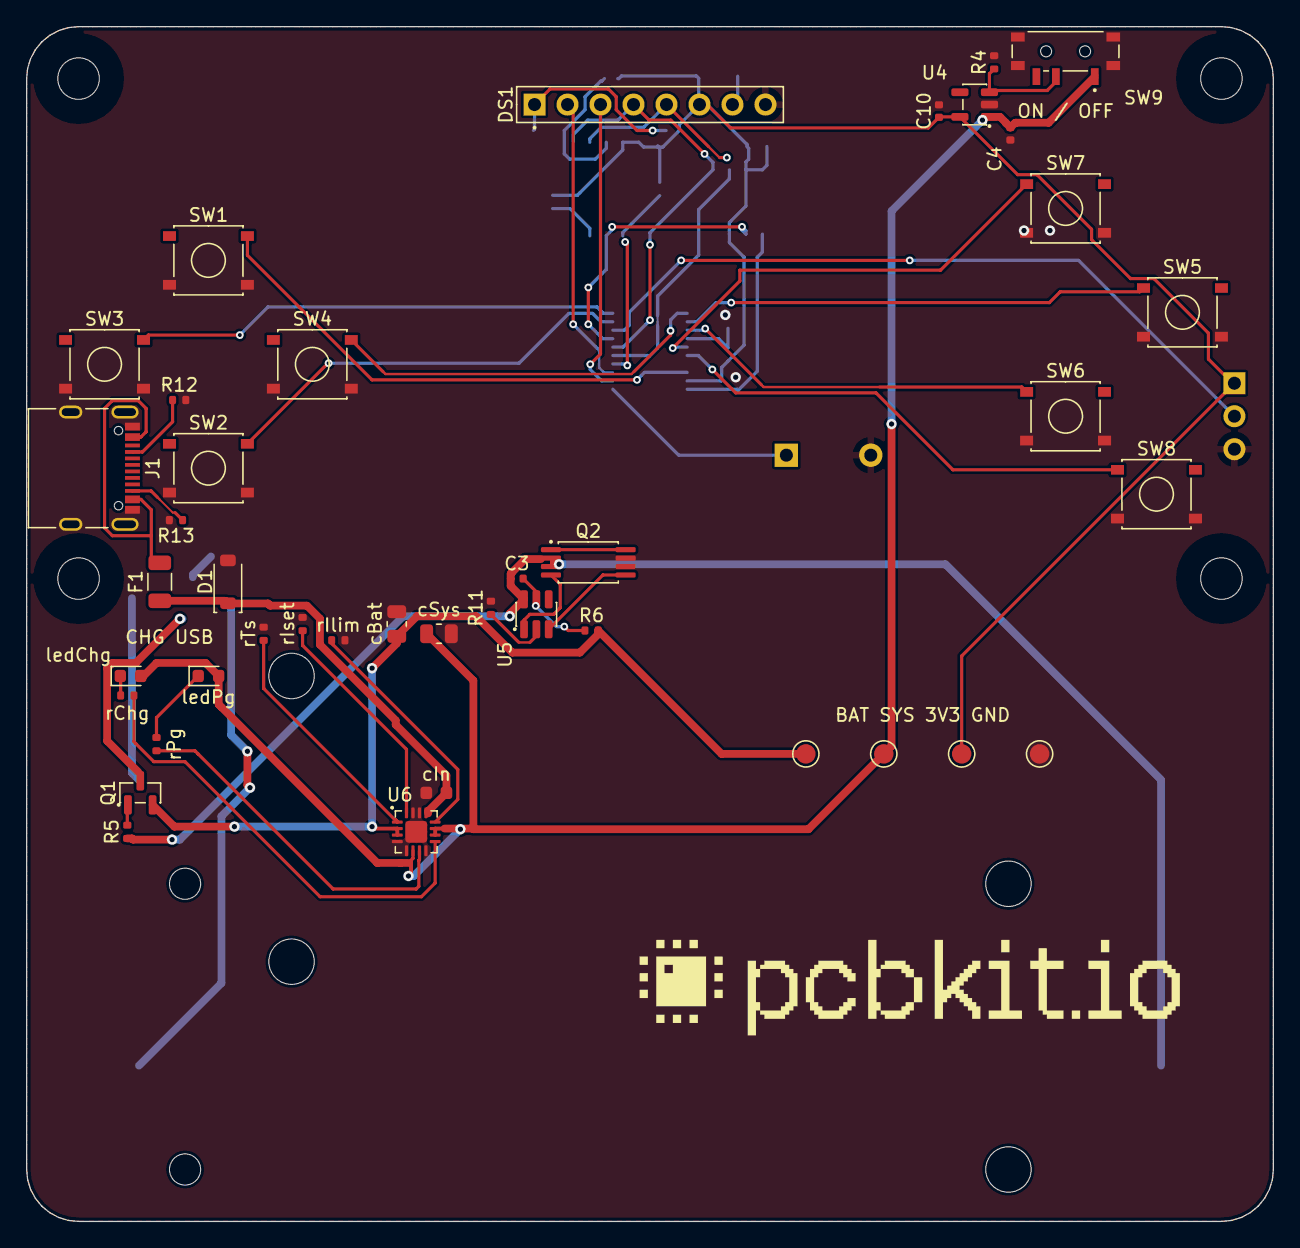
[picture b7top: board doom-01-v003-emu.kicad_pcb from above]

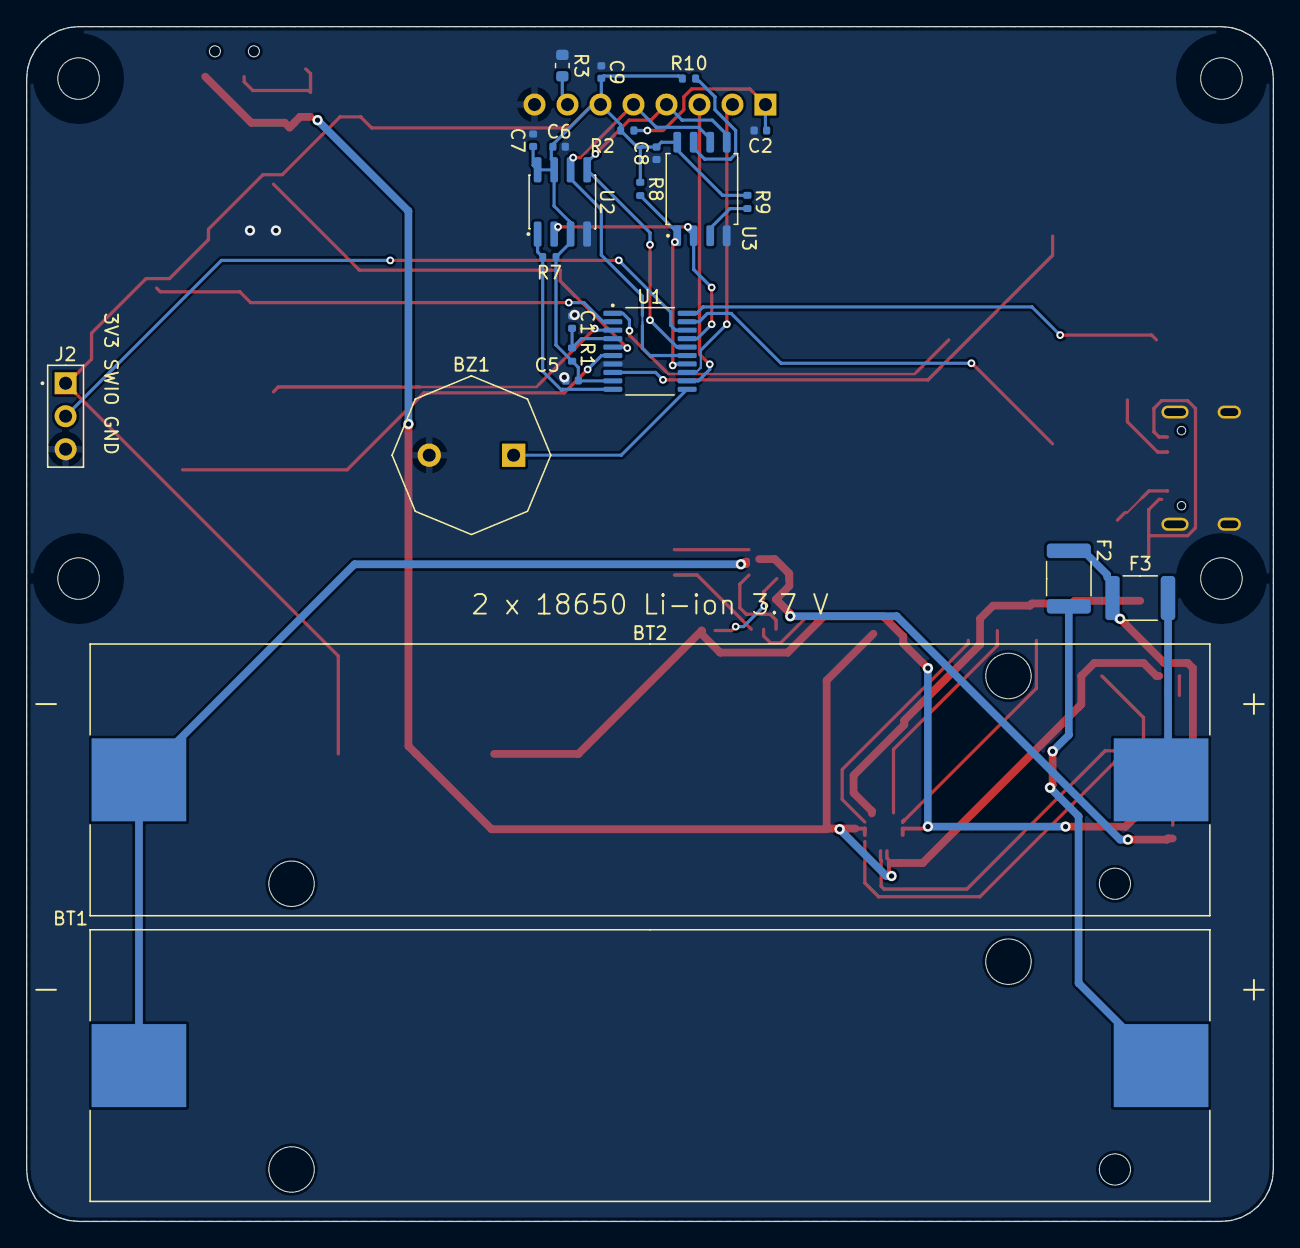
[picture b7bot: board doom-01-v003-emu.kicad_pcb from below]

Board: 2 copper layers, 96.0 x 92.0 mm, 69 parts (23 on the bottom side), 48 nets.

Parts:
BT1, BT2: 1042; BatteryHolder_Keystone_1042_1x18650
BZ1: GPC12075YB-5V4000; Buzzer_D12.0mm_H7.5mm_P6.50mm
C1, C2, C3, C5, C7, C8, C9: 100nF; C_0402_1005Metric
C4, C6, C10: 1uF; C_0402_1005Metric
D1: tvs 5V; D_SOD-123
DS1: Nokia 5110 84x48 LCD module (PCD8544): connector 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; PinHeader_1x08_P2.54mm_Vertical
F1: PTC 750mA; Fuse_1206_3216Metric
F2, F3: PTC 2000mA; Fuse_1812_4532Metric
H1, H2, H3, H4: MountingHole_3.2mm_M3
J1: USB4105-GF-A; USB_C_Receptacle_USB2.0_16P
J2: PinHeader_1x03_P2.54mm_Vertical
Q1: AO3401A; SOT-23
Q2: FS8205A; TSSOP-8_4.4x2.93mm_P0.65mm
R1, R2, R7, R8, R9, R10: 10kohm; R_0402_1005Metric
R3: 330ohm; R_0603_1608Metric
R4: 1Mohm; R_0402_1005Metric
R5: 100kohm; R_0402_1005Metric
R6: 100ohm; R_0402_1005Metric
R11: 1kohm; R_0402_1005Metric
R12, R13: 5.1kohm; R_0402_1005Metric
SW1, SW2, SW3, SW4, SW5, SW6, SW7, SW8: TS-1187A-B-A-B; SW_Tactile_SPST_5.1x5.1mm_SMD
SW9: MSK12C02; SW_Slide_SPDT_Shouhan_MSK12C02
U1: CH32V003F4P6; TSSOP-20_4.4x6.5mm_P0.65mm
U2: APS6404L-3SQR-SN; SOIC-8_3.9x4.9mm_P1.27mm
U3: W25Q128JVSIQ; SOIC-8_5.23x5.28mm_P1.27mm
U4: AP2112K-3.3TRG1; SOT-23-5
U5: DW01A; SOT-6_1.6x2.9mm_P0.95mm
U6: BQ24075RGTR; QFN-16-1EP_3x3mm_P0.5mm_EP1.68x1.68mm
cBat: 4.7uF; C_0805_2012Metric
cIn: 1uF; C_0603_1608Metric
cSys: 4.7uF; C_0805_2012Metric
ledChg: red; LED_0603_1608Metric
ledPg: green; LED_0603_1608Metric
logo: Logo_PCBKit_pcbkit.io
rChg: 1.5kohm; R_0402_1005Metric
rIlim: 1.18kohm; R_0402_1005Metric
rIset: 1.13kohm; R_0402_1005Metric
rPg: 1.5kohm; R_0402_1005Metric
rTs: 10kohm; R_0402_1005Metric
tpBat: TestPoint_Round_D1.5mm
tpGnd: TestPoint_Round_D1.5mm
tpSys: TestPoint_Round_D1.5mm
tpV3: TestPoint_Round_D1.5mm

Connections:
BAT: Q1.2 (S), R6.2 (b), U6.2 (BAT), U6.3 (BAT), cBat.1 (a), tpBat.1
BAT_IN: F2.2 (b), F3.1 (a), Q1.3 (D)
BUZZ: BZ1.1 (A), U1.11 (PC1)
CELL1_P: BT1.2 (C2), F2.1 (a)
CELL2_P: BT2.2 (C2), F3.2 (b)
CELL_N: BT1.1 (C1), BT2.1 (C1), C3.1 (a), Q2.2 (S1), Q2.3 (S1), R5.2 (b), U5.6 (GND)
CHG_LED: ledChg.1 (K), rChg.2 (b)
CHG_N: U6.9 (nCHG), rChg.1 (a)
DOWN: SW2.1 (a), U1.19 (PD2)
FIRE: SW5.1 (a), U1.2 (PD5)
GND: BZ1.2 (B), C1.2 (b), C2.2 (b), C4.2 (b), C5.2 (b), C6.2 (b), C7.2 (b), C8.2 (b), C9.2 (b), C10.2 (b), D1.2 (A), DS1.8 (GND), J1.A1 (GND), J1.A12, J1.B1 (GND), J1.B12, J1.S1 (SHIELD), J2.3, Q2.6 (S2), Q2.7 (S2), R3.2 (b), R4.2 (b), R11.2 (b), R12.2 (b), R13.2 (b), SW1.2 (b), SW2.2 (b), SW3.2 (b), SW4.2 (b), SW5.2 (b), SW6.2 (b), SW7.2 (b), SW8.2 (b), SW9.4 (SHELL), U1.7 (VSS), U2.4 (VSS), U3.4 (GND), U4.2 (GND), U6.4 (nCE), U6.5 (EN2), U6.8 (VSS), U6.14 (TMR), U6.15 (SYSOFF), U6.17 (VSS), cBat.2 (b), cIn.2 (b), cSys.2 (b), rIlim.2 (b), rIset.2 (b), rTs.2 (b), tpGnd.1
ILIM: U6.12 (ILIM), rIlim.1 (a)
ISET: U6.16 (ISET), rIset.1 (a)
LCD_BL: DS1.7 (BL), R3.1 (a)
LCD_CS: DS1.2 (CE), U1.13 (PC3)
LCD_DC: DS1.3 (DC), U1.12 (PC2)
LCD_RST: C2.1 (a), DS1.1 (RST), R2.1 (a)
LDO_EN: R4.1 (a), SW9.2 (COM), U4.3 (EN)
LEFT: SW3.1 (a), U1.20 (PD3)
MENU: SW8.1 (a), U1.6 (PA2)
MISO: U1.17 (PC7), U2.2 (SIO1), U3.2 (DO)
MOSI: DS1.4 (DIN), U1.16 (PC6), U2.5 (SIO0), U3.5 (DI)
NRST: C1.1 (a), R1.2 (b), U1.4 (PD7)
unnamed: C3.2 (b), R6.1 (a), U5.5 (VCC)
unnamed: Q2.4 (G1), U5.1 (OD)
unnamed: Q2.5 (G2), U5.3 (OC)
unnamed: R9.2 (b), U3.3 (nWP)
unnamed: R10.2 (b), U3.7 (nHOLD)
unnamed: R11.1 (a), U5.2 (CS)
PG_LED: ledPg.1 (K), rPg.2 (b)
PG_N: U6.7 (nPGOOD), rPg.1 (a)
RAM_CS: R7.2 (b), U1.10 (PC0), U2.1 (CE)
RIGHT: SW4.1 (a), U1.1 (PD4)
ROM_CS: R8.1 (a), U1.14 (PC4), U3.1 (nCS)
SCK: DS1.5 (CLK), U1.15 (PC5), U2.6 (SCLK), U3.6 (CLK)
STRAFE: SW7.1 (a), U1.5 (PA1)
SWIO: J2.2, U1.18 (PD1)
SYS: C4.1 (a), SW9.1 (A), U4.1 (VIN), U6.6 (EN1), U6.10 (OUT), U6.11 (OUT), cSys.1 (a), ledChg.2 (A), ledPg.2 (A), tpSys.1
TS: U6.1 (TS), rTs.1 (a)
U5Support/DRAIN: Q2.1 (D12), Q2.8 (D12)
UP: SW1.1 (a), U1.8 (PD0)
USE: SW6.1 (a), U1.3 (PD6)
V3: C5.1 (a), C6.1 (a), C7.1 (a), C8.1 (a), C9.1 (a), C10.1 (a), DS1.6 (VCC), J2.1, R1.1 (a), R2.2 (b), R7.1 (a), R8.2 (b), R9.1 (a), R10.1 (a), U1.9 (VDD), U2.3 (SIO2), U2.7 (SIO3), U2.8 (VDD), U3.8 (VCC), U4.5 (VOUT), tpV3.1
VBUS: D1.1 (K), F1.2 (b), U6.13 (IN), cIn.1 (a)
reversed/gate: Q1.1 (G), R5.1 (a)
usb/cc1: J1.A5 (CC1), R12.1 (a)
usb/cc2: J1.B5 (CC2), R13.1 (a)
usb/vbusIn: F1.1 (a), J1.A4 (VBUS), J1.A9, J1.B4 (VBUS), J1.B9

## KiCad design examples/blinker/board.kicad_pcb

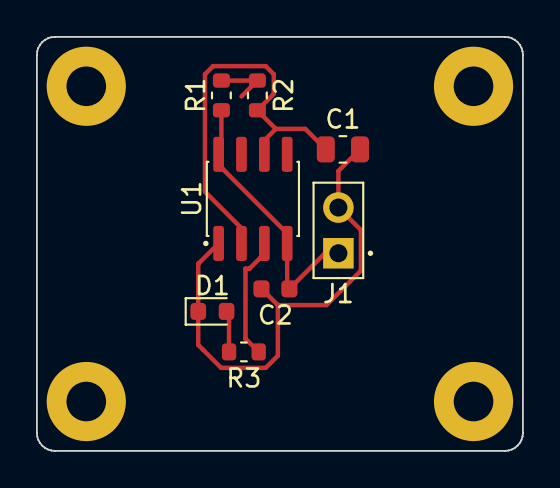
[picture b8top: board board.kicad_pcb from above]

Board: 2 copper layers, 27.0 x 23.0 mm, 12 parts (0 on the bottom side), 6 nets.

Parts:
C1: 10uF; C_0805_2012Metric
C2: 100nF; C_0603_1608Metric
D1: LED_0603_1608Metric
H1, H2, H3, H4: MountingHole_2.2mm_M2_Pad
J1: PinHeader_1x02_P2.54mm_Vertical
R1: 1kohm; R_0603_1608Metric
R2: 10kohm; R_0603_1608Metric
R3: 330ohm; R_0603_1608Metric
U1: NE555DR; SOIC-8_3.9x4.9mm_P1.27mm

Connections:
DIS: R1.2 (b), R2.1 (a), U1.7 (DIS)
GND: C1.2 (b), C2.2 (b), D1.1 (K), J1.2, U1.1 (GND)
LEDK: D1.2 (A), R3.2 (b)
OUT: R3.1 (a), U1.3 (OUT)
TRIG: C1.1 (a), R2.2 (b), U1.2 (TRIG), U1.6 (THR)
VCC: C2.1 (a), J1.1, R1.1 (a), U1.4 (RESET), U1.8 (VCC)

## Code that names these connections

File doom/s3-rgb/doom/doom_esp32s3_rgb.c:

/* Doom's platform layer for doom-09: an ESP32-S3-WROOM-1-N16R8 scanning a raw 4.3" 480 × 272 RGB
 * TFT (Newhaven NHD-4.3-480272EF-ASXP) with LCD_CAM from a frame buffer in its octal PSRAM, and
 * ten buttons on an MCP23017. An ordinary program on the chip's devices:
 *
 *   RGB565 on 16 lines: B3–B7 IO9–IO13, G2–G7 IO7 IO15 IO16 IO17 IO18 IO8, R3–R7 IO1 IO2 IO4 IO5
 *   IO6; PCLK IO42, DE IO40, HSYNC IO39, VSYNC IO41; the backlight's boost enabled on IO46
 *   the MCP23017 at 0x20 on I2C0 (SDA IO14, SCL IO38): forward GPA0, back GPA1, left GPA2,
 *   right GPA3, fire GPA4, use GPA5, strafe left GPA6, strafe right GPB0, menu GPB1, enter GPB2,
 *   each a button to ground on the expander's pull-up
 *
 * The program and the game's data, the shareware DOOM1.WAD (the processor's `data` in the
 * design), run and are read in place from flash through the caches; the zone heap, the screens,
 * the visplanes and the panel's frame are in the PSRAM. LCD_CAM sends the frame by GDMA without
 * end at 8.9 MHz (80 MHz / 9; the panel's typical timing in SYNC-DE mode: HSYNC 4 + 39 + 480 + 8
 * = 531 clocks, 59.7 us a line, VSYNC 4 + 8 + 272 + 8 = 292 lines: 57 Hz);
 * each Doom frame is scaled 1.36 times through the palette into its middle 435 × 272 and written
 * back from the data cache for the DMA to read. Waiting for the next tic sleeps (WAITI until
 * CCOMPARE0). Audio and saved games are absent. The engine is sysprog21/doom_riscv (GPL-2.0) at
 * its pinned revision, its tables const (tables.c/h, r_main.c: in flash) and two arrays in the
 * PSRAM (r_plane.c, w_wad.c). */
#include <stdarg.h>
#include <stdint.h>
#include <stdio.h>
#include <stdlib.h>
#include <string.h>
#include <pcbkit/esp32s3.h>
#include <pcbkit/runtime.h>
#include "doomdef.h"
#include "doomstat.h"
#include "d_main.h"
#include "i_system.h"
#include "i_video.h"
#include "v_video.h"

#define PANEL_W 480
#define PANEL_H 272
#define VIEW_W 435
#define VIEW_X ((PANEL_W - VIEW_W) / 2)
#define BACKLIGHT 46
#define KEYS 0x20
#define BUTTONS 10u
#define TIC_US (1000000u / TICRATE)

static const struct pcbkit_rgb panel = {
    .pclk = 42, .de = 40, .hsync = 39, .vsync = 41, .pclk_neg = 0,
    .data = {9, 10, 11, 12, 13, 7, 15, 16, 17, 18, 8, 1, 2, 4, 5, 6},
    .pclk_hz = 9000000, .width = PANEL_W, .height = PANEL_H,
    .hsw = 4, .hbp = 39, .hfp = 8, .vsw = 4, .vbp = 8, .vfp = 8,
};

static PCBKIT_PSRAM uint16_t frame[PANEL_W * PANEL_H] __attribute__((aligned(64)));
static uint16_t palette565[256];
static uint16_t column_of[VIEW_W];
static uint8_t row_of[PANEL_H];
static uint64_t origin;
static uint32_t held;

static void expander(uint8_t reg, uint8_t a, uint8_t b) {
    const uint8_t bytes[] = {reg, a, b};
    pcbkit_i2c_transfer(KEYS, bytes, 3, NULL, 0);
}

void I_Init(void) { origin = pcbkit_time_us(); }

byte *I_ZoneBase(int *size) {
    *size = 5 * 1024 * 1024;
    return malloc((size_t)*size);
}

/* The current tic. A caller that polls without the tic moving is waiting for the next one:
 * after 16 unchanged polls, sleep until it starts. */
int I_GetTime(void) {
    static uint64_t last = UINT64_MAX;
    static unsigned unchanged;
    uint64_t tic = (pcbkit_time_us() - origin) / TIC_US;
    if (tic != last) {
        unchanged = 0;
    } else if (++unchanged >= 16) {
        pcbkit_sleep_until(origin + (tic + 1) * TIC_US);
        tic = (pcbkit_time_us() - origin) / TIC_US;
        unchanged = 0;
    }
    last = tic;
    return (int)tic;
}

void I_StartFrame(void) {}

/* The buttons, read from the expander's ports each tic (pressed: low). */
void I_StartTic(void) {
    static const int keys[BUTTONS] = {KEY_UPARROW, KEY_DOWNARROW, KEY_LEFTARROW, KEY_RIGHTARROW, KEY_RCTRL, ' ', ',', '.', KEY_ESCAPE, KEY_ENTER};
    uint8_t reg = 0x12, ports[2];
    if (pcbkit_i2c_transfer(KEYS, &reg, 1, ports, 2) != 0) return;
    uint32_t pressed = (~(uint32_t)ports[0] & 0x7fu) | (~(uint32_t)ports[1] & 0x07u) << 7;
    uint32_t changed = pressed ^ held;
    held = pressed;
    for (unsigned i = 0; i < BUTTONS; i++) {
        if (changed & (1u << i)) {
            event_t event = {.type = pressed & (1u << i) ? ev_keydown : ev_keyup, .data1 = keys[i]};
            D_PostEvent(&event);
        }
    }
}

ticcmd_t *I_BaseTiccmd(void) {
    static ticcmd_t empty;
    return &empty;
}

void I_Quit(void) { exit(0); }

/* The four screens (256,000 bytes) in the PSRAM, behind the data cache. */
static PCBKIT_PSRAM byte low[SCREENWIDTH * SCREENHEIGHT * 4];
byte *I_AllocLow(int length) {
    if ((size_t)length <= sizeof low) {
        memset(low, 0, (size_t)length);
        return low;
    }
    return calloc(1, (size_t)length);
}
void I_Tactile(int on, int off, int total) { (void)on; (void)off; (void)total; }

void I_Error(char *format, ...) {
    va_list args;
    va_start(args, format);
    vfprintf(stderr, format, args);
    va_end(args);
    fputc('\n', stderr);
    exit(1);
}

void I_InitGraphics(void) {
    usegamma = 0;
    for (unsigned x = 0; x < VIEW_W; x++) column_of[x] = (uint16_t)(x * SCREENWIDTH / VIEW_W);
    for (unsigned y = 0; y < PANEL_H; y++) row_of[y] = (uint8_t)(y * SCREENHEIGHT / PANEL_H);
    memset(frame, 0, sizeof frame);
    if (pcbkit_rgb_start(&panel, frame) != 0) I_Error("RGB panel: too many DMA descriptors");
    pcbkit_pin_output(BACKLIGHT, 1);
}
void I_ShutdownGraphics(void) {}

void I_SetPalette(byte *palette) {
    for (int i = 0; i < 256; i++, palette += 3) palette565[i] = (uint16_t)((palette[0] & 0xf8) << 8 | (palette[1] & 0xfc) << 3 | palette[2] >> 3);
}

void I_SetRelativeMode(boolean enabled) { (void)enabled; }
void I_MarkDirtyLines(int first, int last) { (void)first; (void)last; }
void I_UpdateNoBlit(void) {}

/* The panel lies turned half a turn (its cable side, the bottom of its own scan, at the board's top
 * edge): the frame goes out from its last pixel to its first. */
void I_FinishUpdate(void) {
    for (unsigned y = 0; y < PANEL_H; y++) {
        const byte *src = screens[0] + row_of[y] * SCREENWIDTH;
        uint16_t *dst = frame + (PANEL_H - 1 - y) * PANEL_W + (PANEL_W - 1 - VIEW_X);
        for (unsigned x = 0; x < VIEW_W; x++) dst[-(int)x] = palette565[src[column_of[x]]];
    }
    pcbkit_cache_writeback(frame, sizeof frame);
}
void I_WaitVBL(int count) { (void)count; }
void I_ReadScreen(byte *dest) { memcpy(dest, screens[0], SCREENWIDTH * SCREENHEIGHT); }
void I_BeginRead(void) {}
void I_EndRead(void) {}

/* No audio. Doom's noise propagation (P_NoiseAlert) is gameplay and stays in the engine. */
int snd_SfxVolume = 0, snd_MusicVolume = 0, numChannels = 0;
void S_Init(int sfx, int music) { (void)sfx; (void)music; }
void S_Start(void) {}
void S_StartSound(void *origin_, int id) { (void)origin_; (void)id; }
void S_StartSoundAtVolume(void *origin_, int id, int volume) { (void)origin_; (void)id; (void)volume; }
void S_StopSound(void *origin_) { (void)origin_; }
void S_StartMusic(int id) { (void)id; }
void S_ChangeMusic(int id, int looping) { (void)id; (void)looping; }
void S_StopMusic(void) {}
void S_PauseSound(void) {}
void S_ResumeSound(void) {}
void S_UpdateSounds(void *listener) { (void)listener; }
void S_SetMusicVolume(int volume) { snd_MusicVolume = volume; }
void S_SetSfxVolume(int volume) { snd_SfxVolume = volume; }
void I_ShutdownSound(void) {}

int main(void) {
    pcbkit_i2c_init(14, 38, 400000);
    expander(0x0c, 0x7f, 0x07); /* GPPUA, GPPUB: pull-ups on the buttons' pins */
    printf("Doom on doom-09 (ESP32-S3, RGB panel): %lu Hz, PSRAM %lu KiB\n", (unsigned long)pcbkit_sys_hz, (unsigned long)(pcbkit_psram_bytes >> 10));
    origin = pcbkit_time_us();
    D_DoomMain();
    return 0;
}
